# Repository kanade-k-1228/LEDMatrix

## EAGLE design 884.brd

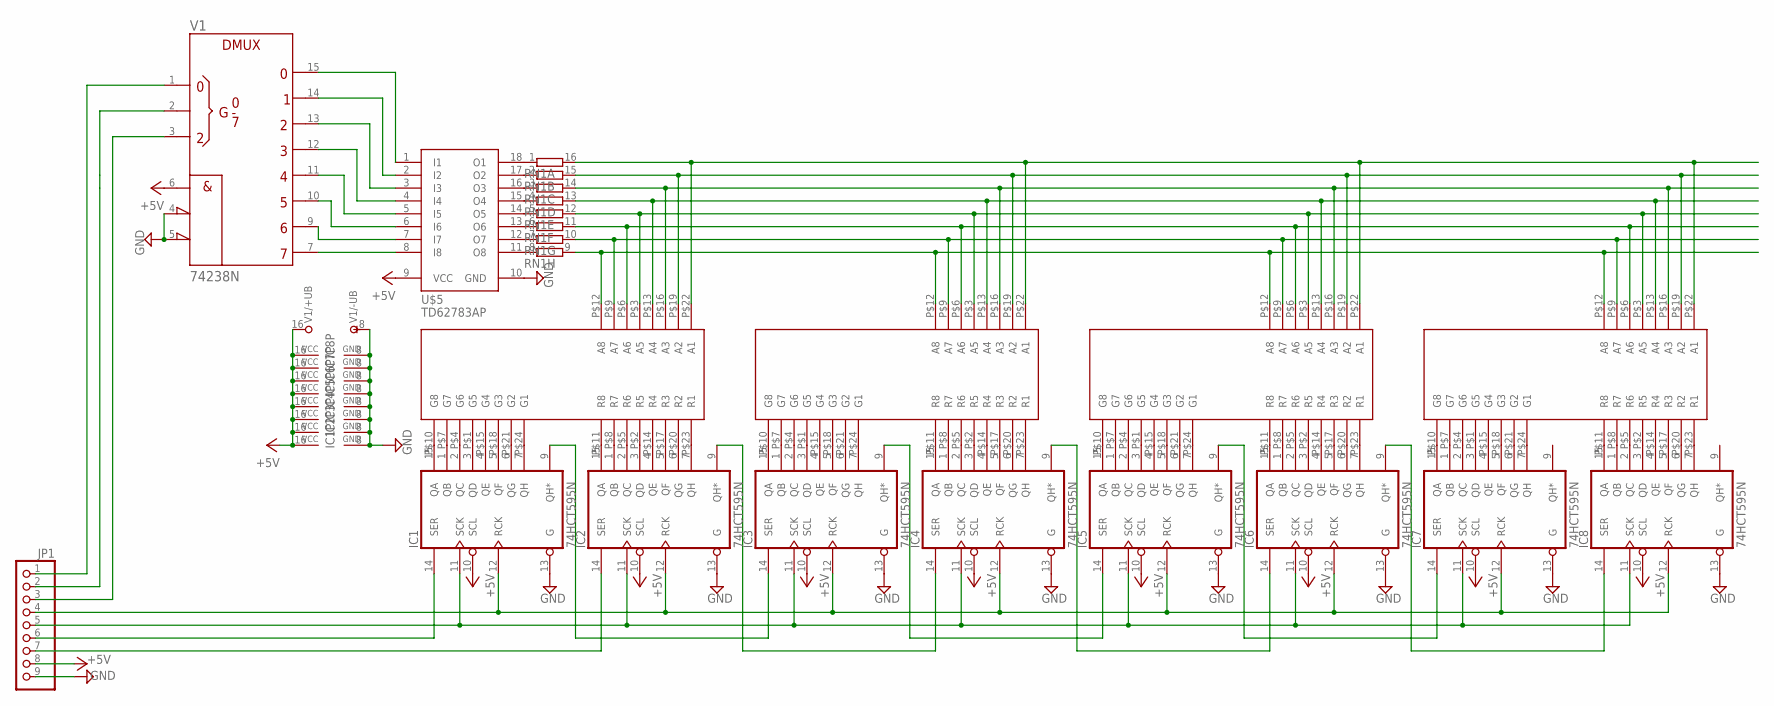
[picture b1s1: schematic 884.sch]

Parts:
IC1, IC2, IC3, IC4, IC5, IC6, IC7, IC8: 74HCT595N; DIL16
JP1: PINHD-1X9; 1X09
RN1: 8R-N; DIL16
U$1, U$2, U$3, U$4: LED_ARRAY_8X8; 2.54*11-24
U$5: TD62783AP; DIL18
V1: 74238N; DIL16

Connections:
+5V: IC1.10 (SCL), IC1.16 (VCC), IC2.10 (SCL), IC2.16 (VCC), IC3.10 (SCL), IC3.16 (VCC), IC4.10 (SCL), IC4.16 (VCC), IC5.10 (SCL), IC5.16 (VCC), IC6.10 (SCL), IC6.16 (VCC), IC7.10 (SCL), IC7.16 (VCC), IC8.10 (SCL), IC8.16 (VCC), JP1.8, U$5.9 (VCC), V1.6 (G1), V1.16 (+UB)
GND: IC1.8 (GND), IC1.13 (G), IC2.8 (GND), IC2.13 (G), IC3.8 (GND), IC3.13 (G), IC4.8 (GND), IC4.13 (G), IC5.8 (GND), IC5.13 (G), IC6.8 (GND), IC6.13 (G), IC7.8 (GND), IC7.13 (G), IC8.8 (GND), IC8.13 (G), JP1.9, U$5.10 (GND), V1.4 (!G2A), V1.5 (!G2B), V1.8 (-UB)
unnamed: IC1.1 (QB), U$1.P$7 (G7)
unnamed: IC1.2 (QC), U$1.P$4 (G6)
unnamed: IC1.3 (QD), U$1.P$1 (G5)
unnamed: IC1.4 (QE), U$1.P$15 (G4)
unnamed: IC1.5 (QF), U$1.P$18 (G3)
unnamed: IC1.6 (QG), U$1.P$21 (G2)
unnamed: IC1.7 (QH), U$1.P$24 (G1)
unnamed: IC1.15 (QA), U$1.P$10 (G8)
unnamed: IC2.1 (QB), U$1.P$8 (R7)
unnamed: IC2.2 (QC), U$1.P$5 (R6)
unnamed: IC2.3 (QD), U$1.P$2 (R5)
unnamed: IC2.4 (QE), U$1.P$14 (R4)
unnamed: IC2.5 (QF), U$1.P$17 (R3)
unnamed: IC2.6 (QG), U$1.P$20 (R2)
unnamed: IC2.7 (QH), U$1.P$23 (R1)
unnamed: IC2.15 (QA), U$1.P$11 (R8)
unnamed: IC2.14 (SER), JP1.7
unnamed: IC3.1 (QB), U$2.P$7 (G7)
unnamed: IC3.2 (QC), U$2.P$4 (G6)
unnamed: IC3.3 (QD), U$2.P$1 (G5)
unnamed: IC3.4 (QE), U$2.P$15 (G4)
unnamed: IC3.5 (QF), U$2.P$18 (G3)
unnamed: IC3.6 (QG), U$2.P$21 (G2)
unnamed: IC3.7 (QH), U$2.P$24 (G1)
unnamed: IC3.15 (QA), U$2.P$10 (G8)
unnamed: IC4.1 (QB), U$2.P$8 (R7)
unnamed: IC4.2 (QC), U$2.P$5 (R6)
unnamed: IC4.3 (QD), U$2.P$2 (R5)
unnamed: IC4.4 (QE), U$2.P$14 (R4)
unnamed: IC4.5 (QF), U$2.P$17 (R3)
unnamed: IC4.6 (QG), U$2.P$20 (R2)
unnamed: IC4.7 (QH), U$2.P$23 (R1)
unnamed: IC4.15 (QA), U$2.P$11 (R8)
unnamed: IC1.14 (SER), JP1.6
unnamed: IC5.1 (QB), U$3.P$7 (G7)
unnamed: IC5.2 (QC), U$3.P$4 (G6)
unnamed: IC5.3 (QD), U$3.P$1 (G5)
unnamed: IC5.4 (QE), U$3.P$15 (G4)
unnamed: IC5.5 (QF), U$3.P$18 (G3)
unnamed: IC5.6 (QG), U$3.P$21 (G2)
unnamed: IC5.7 (QH), U$3.P$24 (G1)
unnamed: IC5.15 (QA), U$3.P$10 (G8)
unnamed: IC6.1 (QB), U$3.P$8 (R7)
unnamed: IC6.2 (QC), U$3.P$5 (R6)
unnamed: IC6.3 (QD), U$3.P$2 (R5)
unnamed: IC6.4 (QE), U$3.P$14 (R4)
unnamed: IC6.5 (QF), U$3.P$17 (R3)
unnamed: IC6.6 (QG), U$3.P$20 (R2)
unnamed: IC6.7 (QH), U$3.P$23 (R1)
unnamed: IC6.15 (QA), U$3.P$11 (R8)
unnamed: IC2.9 (QH*), IC4.14 (SER)
unnamed: IC7.1 (QB), U$4.P$7 (G7)
unnamed: IC7.2 (QC), U$4.P$4 (G6)
unnamed: IC7.3 (QD), U$4.P$1 (G5)
unnamed: IC7.4 (QE), U$4.P$15 (G4)
unnamed: IC7.5 (QF), U$4.P$18 (G3)
unnamed: IC7.6 (QG), U$4.P$21 (G2)
unnamed: IC7.7 (QH), U$4.P$24 (G1)
unnamed: IC7.15 (QA), U$4.P$10 (G8)
unnamed: IC8.1 (QB), U$4.P$8 (R7)
unnamed: IC8.2 (QC), U$4.P$5 (R6)
unnamed: IC8.3 (QD), U$4.P$2 (R5)
unnamed: IC8.4 (QE), U$4.P$14 (R4)
unnamed: IC8.5 (QF), U$4.P$17 (R3)
unnamed: IC8.6 (QG), U$4.P$20 (R2)
unnamed: IC8.7 (QH), U$4.P$23 (R1)
unnamed: IC8.15 (QA), U$4.P$11 (R8)
unnamed: IC3.9 (QH*), IC5.14 (SER)
unnamed: IC4.9 (QH*), IC6.14 (SER)
unnamed: IC5.9 (QH*), IC7.14 (SER)
unnamed: IC6.9 (QH*), IC8.14 (SER)
unnamed: U$5.8 (I8), V1.7 (Y7)
unnamed: U$5.7 (I7), V1.9 (Y6)
unnamed: U$5.6 (I6), V1.10 (Y5)
unnamed: U$5.5 (I5), V1.11 (Y4)
unnamed: U$5.4 (I4), V1.12 (Y3)
unnamed: U$5.3 (I3), V1.13 (Y2)
unnamed: U$5.2 (I2), V1.14 (Y1)
unnamed: U$5.1 (I1), V1.15 (Y0)
unnamed: IC1.12 (RCK), IC2.12 (RCK), IC3.12 (RCK), IC4.12 (RCK), IC5.12 (RCK), IC6.12 (RCK), IC7.12 (RCK), IC8.12 (RCK), JP1.4
unnamed: IC1.11 (SCK), IC2.11 (SCK), IC3.11 (SCK), IC4.11 (SCK), IC5.11 (SCK), IC6.11 (SCK), IC7.11 (SCK), IC8.11 (SCK), JP1.5
unnamed: RN1.1, U$5.18 (O1)
unnamed: RN1.2 (1), U$5.17 (O2)
unnamed: RN1.3 (1), U$5.16 (O3)
unnamed: RN1.4 (1), U$5.15 (O4)
unnamed: RN1.5 (1), U$5.14 (O5)
unnamed: RN1.6 (1), U$5.13 (O6)
unnamed: RN1.7 (1), U$5.12 (O7)
unnamed: RN1.8 (1), U$5.11 (O8)
unnamed: RN1.16 (2), U$1.P$22 (A1), U$2.P$22 (A1), U$3.P$22 (A1), U$4.P$22 (A1)
unnamed: RN1.15 (2), U$1.P$19 (A2), U$2.P$19 (A2), U$3.P$19 (A2), U$4.P$19 (A2)
unnamed: RN1.14 (2), U$1.P$16 (A3), U$2.P$16 (A3), U$3.P$16 (A3), U$4.P$16 (A3)
unnamed: RN1.13 (2), U$1.P$13 (A4), U$2.P$13 (A4), U$3.P$13 (A4), U$4.P$13 (A4)
unnamed: RN1.12 (2), U$1.P$3 (A5), U$2.P$3 (A5), U$3.P$3 (A5), U$4.P$3 (A5)
unnamed: RN1.11 (2), U$1.P$6 (A6), U$2.P$6 (A6), U$3.P$6 (A6), U$4.P$6 (A6)
unnamed: RN1.10 (2), U$1.P$9 (A7), U$2.P$9 (A7), U$3.P$9 (A7), U$4.P$9 (A7)
unnamed: RN1.9 (2), U$1.P$12 (A8), U$2.P$12 (A8), U$3.P$12 (A8), U$4.P$12 (A8)
unnamed: JP1.3, V1.3 (C)
unnamed: JP1.2, V1.2 (B)
unnamed: JP1.1, V1.1 (A)
unnamed: IC1.9 (QH*), IC3.14 (SER)

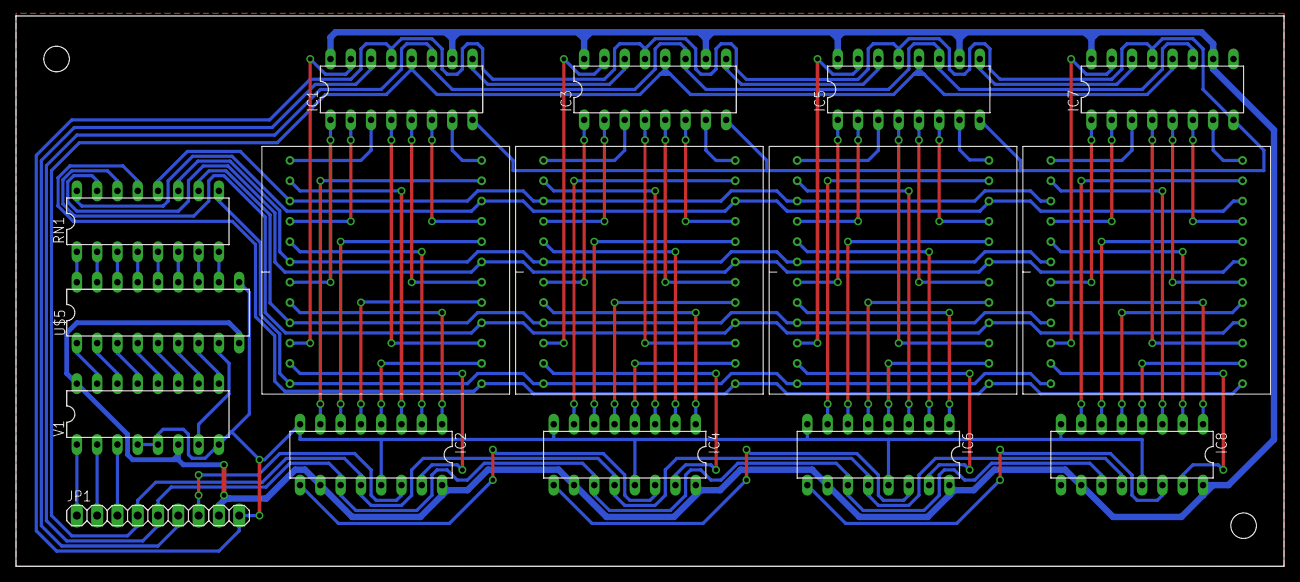
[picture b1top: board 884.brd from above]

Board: 2 copper layers, 158.7 x 68.9 mm, 18 parts (0 on the bottom side), 103 nets.

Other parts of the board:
U$6, U$7: HOLE_3.2

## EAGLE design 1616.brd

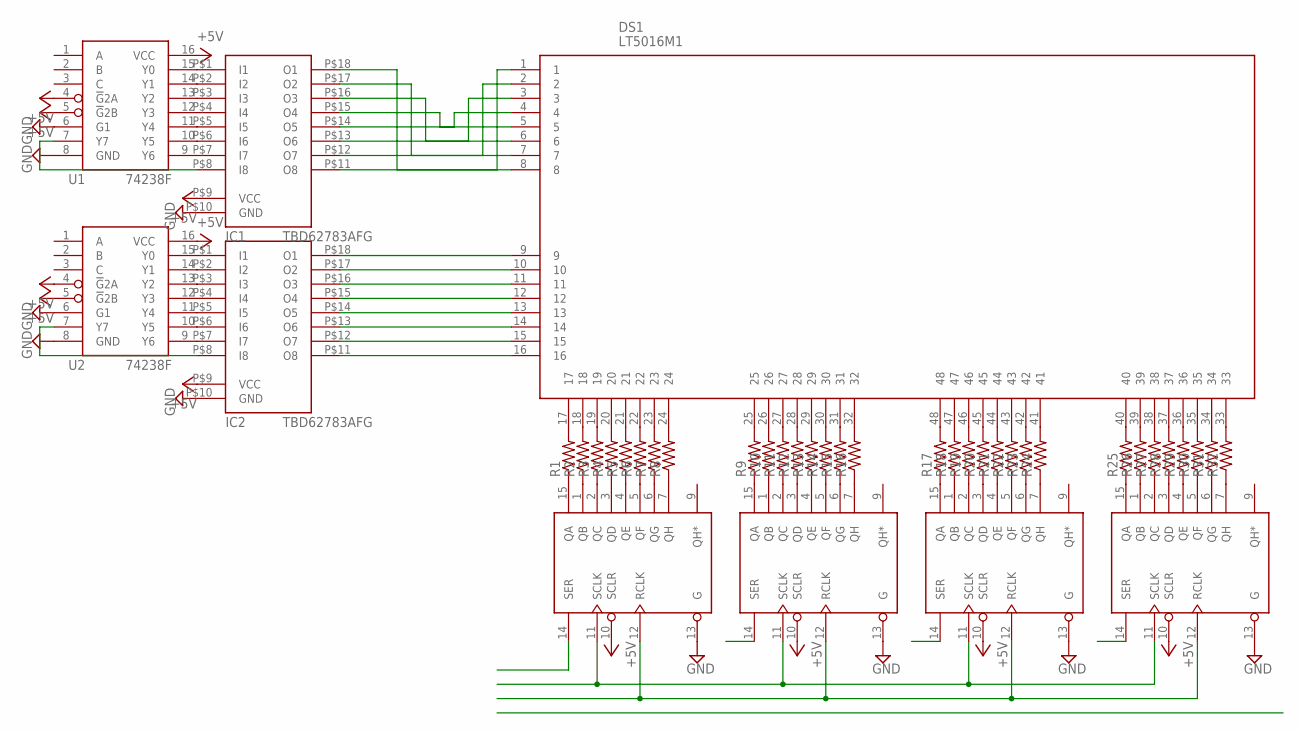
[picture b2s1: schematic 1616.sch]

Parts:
DS1: LT5016M1
IC1, IC2: TBD62783AFG; SOP18
R1, R2, R3, R4, R5, R6, R7, R8, R9, R10, R11, R12, R13, R14, R15, R16, R17, R18, R19, R20, R21, R22, R23, R24, R25, R26, R27, R28, R29, R30, R31, R32: R-2012; 2012-R
U1, U2: 74238F; SOP16
U$1, U$2, U$3, U$4: 74HC595N; DIL16

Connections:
+5V: IC1.P$9 (VCC), IC2.P$9 (VCC), U1.4 (!G!2A), U1.5 (!G!2B), U1.16 (VCC), U2.4 (!G!2A), U2.5 (!G!2B), U2.16 (VCC), U$1.10 (SCLR), U$2.10 (SCLR), U$3.10 (SCLR), U$4.10 (SCLR)
GND: IC1.P$10 (GND), IC2.P$10 (GND), U1.6 (G1), U1.8 (GND), U2.6 (G1), U2.8 (GND), U$1.8 (GND), U$1.13 (G), U$2.8 (GND), U$2.13 (G), U$3.8 (GND), U$3.13 (G), U$4.8 (GND), U$4.13 (G)
unnamed: DS1.24, R8.2
unnamed: DS1.25, R9.2
unnamed: DS1.26, R10.2
unnamed: DS1.17, R1.2
unnamed: DS1.18, R2.2
unnamed: DS1.19, R3.2
unnamed: DS1.20, R4.2
unnamed: DS1.21, R5.2
unnamed: DS1.22, R6.2
unnamed: DS1.23, R7.2
unnamed: DS1.27, R11.2
unnamed: DS1.28, R12.2
unnamed: DS1.29, R13.2
unnamed: DS1.30, R14.2
unnamed: DS1.31, R15.2
unnamed: DS1.32, R16.2
unnamed: DS1.48, R17.2
unnamed: DS1.47, R18.2
unnamed: DS1.46, R19.2
unnamed: DS1.45, R20.2
unnamed: DS1.44, R21.2
unnamed: DS1.43, R22.2
unnamed: DS1.42, R23.2
unnamed: DS1.41, R24.2
unnamed: DS1.40, R25.2
unnamed: DS1.39, R26.2
unnamed: DS1.38, R27.2
unnamed: DS1.37, R28.2
unnamed: DS1.36, R29.2
unnamed: DS1.35, R30.2
unnamed: DS1.34, R31.2
unnamed: DS1.33, R32.2
unnamed: DS1.1, IC1.P$11 (O8)
unnamed: U$1.11 (SCLK), U$2.11 (SCLK), U$3.11 (SCLK), U$4.11 (SCLK)
unnamed: U$1.12 (RCLK), U$2.12 (RCLK), U$3.12 (RCLK), U$4.12 (RCLK)
unnamed: DS1.2, IC1.P$12 (O7)
unnamed: DS1.3, IC1.P$13 (O6)
unnamed: DS1.4, IC1.P$14 (O5)
unnamed: DS1.5, IC1.P$15 (O4)
unnamed: DS1.6, IC1.P$16 (O3)
unnamed: DS1.7, IC1.P$17 (O2)
unnamed: DS1.8, IC1.P$18 (O1)
unnamed: DS1.9, IC2.P$18 (O1)
unnamed: DS1.10, IC2.P$17 (O2)
unnamed: DS1.11, IC2.P$16 (O3)
unnamed: DS1.12, IC2.P$15 (O4)
unnamed: DS1.13, IC2.P$14 (O5)
unnamed: DS1.14, IC2.P$13 (O6)
unnamed: DS1.15, IC2.P$12 (O7)
unnamed: DS1.16, IC2.P$11 (O8)
unnamed: IC1.P$7 (I7), U1.9 (Y6)
unnamed: IC1.P$6 (I6), U1.10 (Y5)
unnamed: IC1.P$5 (I5), U1.11 (Y4)
unnamed: IC1.P$4 (I4), U1.12 (Y3)
unnamed: IC1.P$3 (I3), U1.13 (Y2)
unnamed: IC1.P$2 (I2), U1.14 (Y1)
unnamed: IC1.P$1 (I1), U1.15 (Y0)
unnamed: IC2.P$7 (I7), U2.9 (Y6)
unnamed: IC2.P$6 (I6), U2.10 (Y5)
unnamed: IC2.P$5 (I5), U2.11 (Y4)
unnamed: IC2.P$4 (I4), U2.12 (Y3)
unnamed: IC2.P$3 (I3), U2.13 (Y2)
unnamed: IC2.P$2 (I2), U2.14 (Y1)
unnamed: IC2.P$1 (I1), U2.15 (Y0)
unnamed: R1.1, U$1.15 (QA)
unnamed: R2.1, U$1.1 (QB)
unnamed: R3.1, U$1.2 (QC)
unnamed: R4.1, U$1.3 (QD)
unnamed: R5.1, U$1.4 (QE)
unnamed: R6.1, U$1.5 (QF)
unnamed: R7.1, U$1.6 (QG)
unnamed: R8.1, U$1.7 (QH)
unnamed: R9.1, U$2.15 (QA)
unnamed: R10.1, U$2.1 (QB)
unnamed: R11.1, U$2.2 (QC)
unnamed: R12.1, U$2.3 (QD)
unnamed: R13.1, U$2.4 (QE)
unnamed: R14.1, U$2.5 (QF)
unnamed: R15.1, U$2.6 (QG)
unnamed: R16.1, U$2.7 (QH)
unnamed: R17.1, U$3.15 (QA)
unnamed: R18.1, U$3.1 (QB)
unnamed: R19.1, U$3.2 (QC)
unnamed: R20.1, U$3.3 (QD)
unnamed: R21.1, U$3.4 (QE)
unnamed: R22.1, U$3.5 (QF)
unnamed: R23.1, U$3.6 (QG)
unnamed: R24.1, U$3.7 (QH)
unnamed: R25.1, U$4.15 (QA)
unnamed: R26.1, U$4.1 (QB)
unnamed: R27.1, U$4.2 (QC)
unnamed: R28.1, U$4.3 (QD)
unnamed: R29.1, U$4.4 (QE)
unnamed: R30.1, U$4.5 (QF)
unnamed: R31.1, U$4.6 (QG)
unnamed: R32.1, U$4.7 (QH)
unnamed: IC2.P$8 (I8), U2.7 (Y7)
unnamed: IC1.P$8 (I8), U1.7 (Y7)
VCC: U$1.16 (VCC), U$2.16 (VCC), U$3.16 (VCC), U$4.16 (VCC)

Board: 2 copper layers, 41 parts (36 on the bottom side), 101 nets, no tracks yet.

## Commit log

2019-12-03 copy
